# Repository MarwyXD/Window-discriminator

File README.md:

# Window-discriminator

# The window discriminator is only a voltage comparator with not only one voltage level, but two voltage levels. If you for example chose 0.7V and 3.3V levels, if you will be in between this range of voltages you can do something, if not do something else.

# I created this as if i´m in the range it goes to the OR gate (7432) and INV (7404 - the output of the OPAmp is low in between) and it lights one LED - and so on for other three voltage windows. If all four windows are activated (leds are glowing), i added 4NAND (7420) and INV to count all the on outputs and multiply them together = if all of them are on, the output will be on too, so the fifth LED is glowing too - it signals that all windows are acitve.

# If i´m not in the range the the LEDs are not glowing.

# My motivation for doing this relatively "complicated" circuit was the fact that i saw the TCA965B chip (originaly designed to be a window comparator), but its not available for me, so i said to my self, hey let´s create something at least something similar to it.

# It has some mistake, as the biggest one (not destructing but on the top of what the ICs can hold) i see that id didnt gave any 5.1V zener diodes after the outputs of the LM324, second is due to big supp voltage (20V) the LM324 is geting hot (again, not destructive, but to the limits)

# The schematic is available to all of you (as well as the rest of the zip file), but you can create your own and better schematic/PCB.

# Thank you.

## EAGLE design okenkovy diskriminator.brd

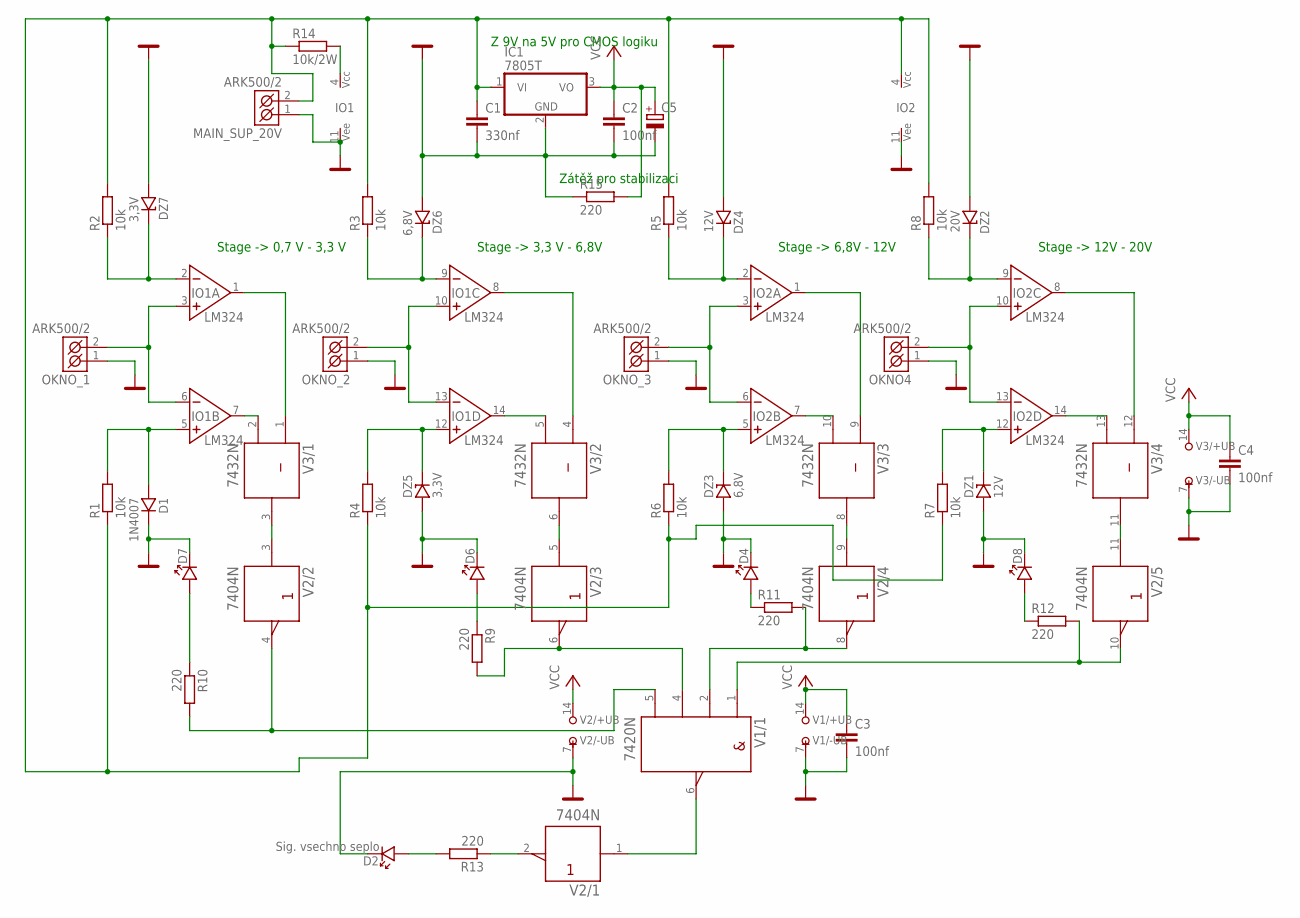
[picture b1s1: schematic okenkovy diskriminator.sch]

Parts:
C1: 330nf; C050-030X075
C2: 100nf; C050-030X075
C3, C4: 100nf; C050-025X075
C5: CPOL-EUE2.5-5; E2,5-5
D1: 1N4007; DO41
D2: Sig. vsechno seplo; LED_5
D4, D6, D7, D8: LED_5
DZ1, DZ4: 12V; DO35
DZ2: 20V; DO35
DZ3, DZ6: 6,8V; DO35
DZ5, DZ7: 3,3V; DO35
IC1: 7805T; TO220H
IO1, IO2: LM324; DIL14
MAIN_SUP_20V: ARK500/2
OKNO4: ARK500/2
OKNO_1, OKNO_2, OKNO_3: ARK500/2
R1, R2, R3, R4, R5, R6, R7, R8: 10k; 0207/10
R9, R10, R11, R12, R13, R15: 220; 0207/10
R14: 10k/2W; 0414/15
V1: 7420N; DIL14
V2: 7404N; DIL14
V3: 7432N; DIL14

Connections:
GND: C1.2, C2.2, C3.2, C4.2, C5.-, D1.K, D2.K, D4.K, D6.K, D7.K, D8.K, DZ1.A, DZ2.A, DZ3.A, DZ4.A, DZ5.A, DZ6.A, DZ7.A, IC1.2 (GND), IO1.11 (VEE), IO2.11 (VEE), MAIN_SUP_20V.1 (K1), OKNO4.1 (K1), OKNO_1.1 (K1), OKNO_2.1 (K1), OKNO_3.1 (K1), R15.1, V1.7 (-UB), V2.7 (-UB), V3.7 (-UB)
unnamed: D1.A, IO1.5 (NEIN+), R1.2
unnamed: DZ7.K, IO1.2 (IN-), R2.1
unnamed: DZ6.K, IO1.9 (IN-), R3.1
unnamed: DZ5.K, IO1.12 (NEIN+), R4.2
unnamed: DZ3.K, IO2.5 (NEIN+), R6.2
unnamed: DZ4.K, IO2.2 (IN-), R5.1
unnamed: DZ1.K, IO2.12 (NEIN+), R7.2
unnamed: DZ2.K, IO2.9 (IN-), R8.1
unnamed: IO1.3 (NEIN+), IO1.6 (IN-), OKNO_1.2 (K2)
unnamed: IO1.10 (NEIN+), IO1.13 (IN-), OKNO_2.2 (K2)
unnamed: IO2.3 (NEIN+), IO2.6 (IN-), OKNO_3.2 (K2)
unnamed: IO2.10 (NEIN+), IO2.13 (IN-), OKNO4.2 (K2)
unnamed: IO1.1 (VYSTUP), V3.1 (A)
unnamed: D7.A, R10.1
unnamed: IO1.7 (VYSTUP), V3.2 (B)
unnamed: D6.A, R9.1
unnamed: IO1.8 (VYSTUP), V3.4 (A)
unnamed: D4.A, R11.1
unnamed: IO1.14 (VYSTUP), V3.5 (B)
unnamed: D8.A, R12.1
unnamed: IO2.1 (VYSTUP), V3.9 (A)
unnamed: R13.1, V2.2 (Y)
unnamed: IO2.7 (VYSTUP), V3.10 (B)
unnamed: D2.A, R13.2
unnamed: IO2.8 (VYSTUP), V3.12 (A)
unnamed: IO2.14 (VYSTUP), V3.13 (B)
unnamed: V2.11 (A), V3.11 (Y)
unnamed: V2.9 (A), V3.8 (Y)
unnamed: R9.2, V1.4 (C), V2.6 (Y)
unnamed: V2.5 (A), V3.6 (Y)
unnamed: R10.2, V1.5 (D), V2.4 (Y)
unnamed: IO1.4 (VCC), R14.2
unnamed: R11.2, V1.2 (B), V2.8 (Y)
unnamed: R12.2, V1.1 (A), V2.10 (Y)
unnamed: V2.3 (A), V3.3 (Y)
unnamed: V1.6 (Y), V2.1 (A)
unnamed: C1.1, IC1.1 (VI), IO2.4 (VCC), MAIN_SUP_20V.2 (K2), R1.1, R2.2, R3.2, R4.1, R5.2, R6.1, R7.1, R8.2, R14.1
VCC: C2.1, C3.1, C4.1, C5.+, IC1.3 (VO), R15.2, V1.14 (+UB), V2.14 (+UB), V3.14 (+UB)

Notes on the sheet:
Stage -> 0,7 V - 3,3 V
Stage -> 3,3 V - 6,8V
Stage -> 6,8V - 12V
Stage -> 12V - 20V
Z 9V na 5V pro CMOS logiku
Zátěž pro stabilizaci

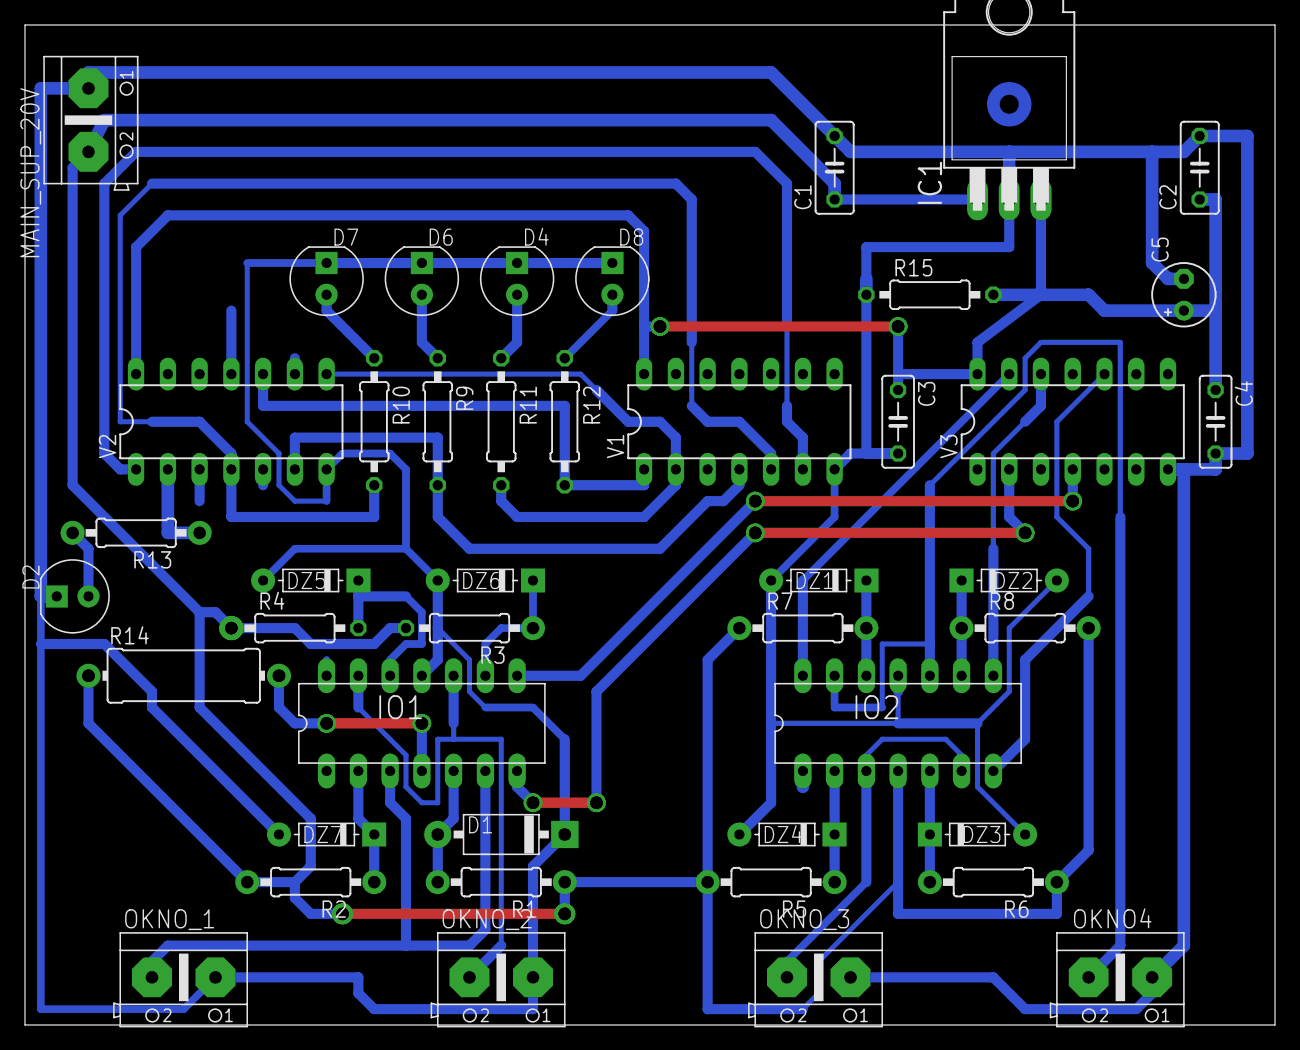
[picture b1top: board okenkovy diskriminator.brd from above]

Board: 2 copper layers, 100.0 x 80.0 mm, 44 parts (0 on the bottom side), 39 nets.

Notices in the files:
parts and their libraries:
Copyright (C) PaJa 2001-2014
Copyright (C) PaJa 2011-2014
